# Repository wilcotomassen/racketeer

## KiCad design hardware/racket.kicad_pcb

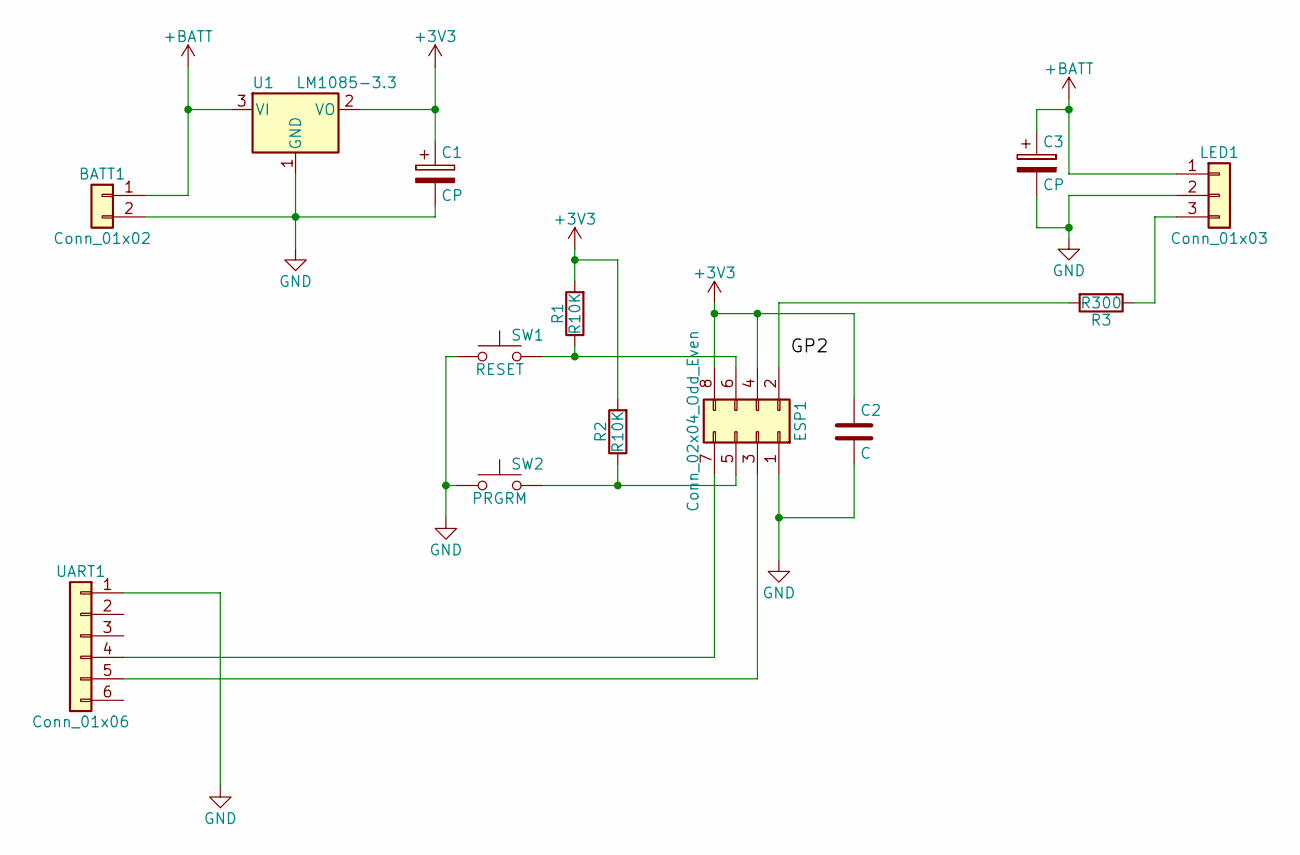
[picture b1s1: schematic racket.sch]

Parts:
BATT1: Conn_01x02; Pin_Header_Straight_1x02_Pitch2.54mm
C1, C3: CP; CP_Radial_D6.3mm_P2.50mm
C2: C; C_Rect_L7.0mm_W3.5mm_P5.00mm
ESP1: Conn_02x04_Odd_Even; Pin_Header_Straight_2x04_Pitch2.54mm
LED1: Conn_01x03; Pin_Header_Straight_1x03_Pitch2.54mm
R1, R2: R10K; R_Axial_DIN0204_L3.6mm_D1.6mm_P1.90mm_Vertical
R3: R300; R_Axial_DIN0204_L3.6mm_D1.6mm_P1.90mm_Vertical
SW1: RESET; SW_TH_Tactile_Omron_B3F-10xx
SW2: PRGRM; SW_TH_Tactile_Omron_B3F-10xx
U1: LM1085-3.3; TO-220-3_Horizontal
UART1: Conn_01x06; Pin_Header_Angled_1x06_Pitch2.54mm

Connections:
+3V3: C1.1, C2.1, ESP1.4, ESP1.8, R1.2, R2.2, U1.2 (VO)
+BATT: BATT1.1, C3.1, LED1.1, U1.3 (VI)
GND: BATT1.2, C1.2, C2.2, C3.2, ESP1.1, LED1.2, SW1.1, SW2.1, U1.1 (GND), UART1.1
unnamed: ESP1.2, R3.2
unnamed: ESP1.3, UART1.5
unnamed: ESP1.5, R2.1, SW2.2
unnamed: ESP1.6, R1.1, SW1.2
unnamed: ESP1.7, UART1.4
unnamed: LED1.3, R3.1

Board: 2 copper layers, 13 parts (1 on the bottom side), 9 nets, no tracks yet.

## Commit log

2018-09-21 Initial firmware (ESP01 blink)
2018-09-21 Added WIFI connect example to firmware
2018-09-21 Added WIFI UDP receiving
2018-09-27 Updated firmware
2018-09-27 Added P5 server
2018-09-27 Initial server
2018-09-27 Hardware
2018-09-27 Final tweaks
2018-09-27 Added pos to ball
2018-10-01 Added board settings
2018-10-01 Visual tweaks on history drawing
